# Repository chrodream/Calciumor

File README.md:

# Calciumor
## 特徴
- ESP32-S3をベースとした電卓\/無線マクロパッド
- Li-Poバッテリーによる充電に対応
- 128×64ドットのOLED表示 or 128×32ドット + 7セグ表示器

## スペック
| 項目 | Min. | Typ. | Max. | 
| :------------------------ | ---- | ---- | ---- | 
| USB入力電圧 [V] | 4.75 | 5.0 | 5.25 | 
| 消費電流 (電卓/バッテリー) [mA] | | | | 
| 消費電流(マクロパッド/バッテリー) [mA] | | | |
| 消費電流 (電卓/USB) [mA] | | | 750 |
| 消費電流(マクロパッド/USB) [mA]   | | | 750 |
| 消費電流(スリープ) [mA]    | | | | 
| バッテリー容量 [mAh] | 400 | - | - | 
| バッテリー電圧範囲 [V] | 2.9 | - | 4.2 |

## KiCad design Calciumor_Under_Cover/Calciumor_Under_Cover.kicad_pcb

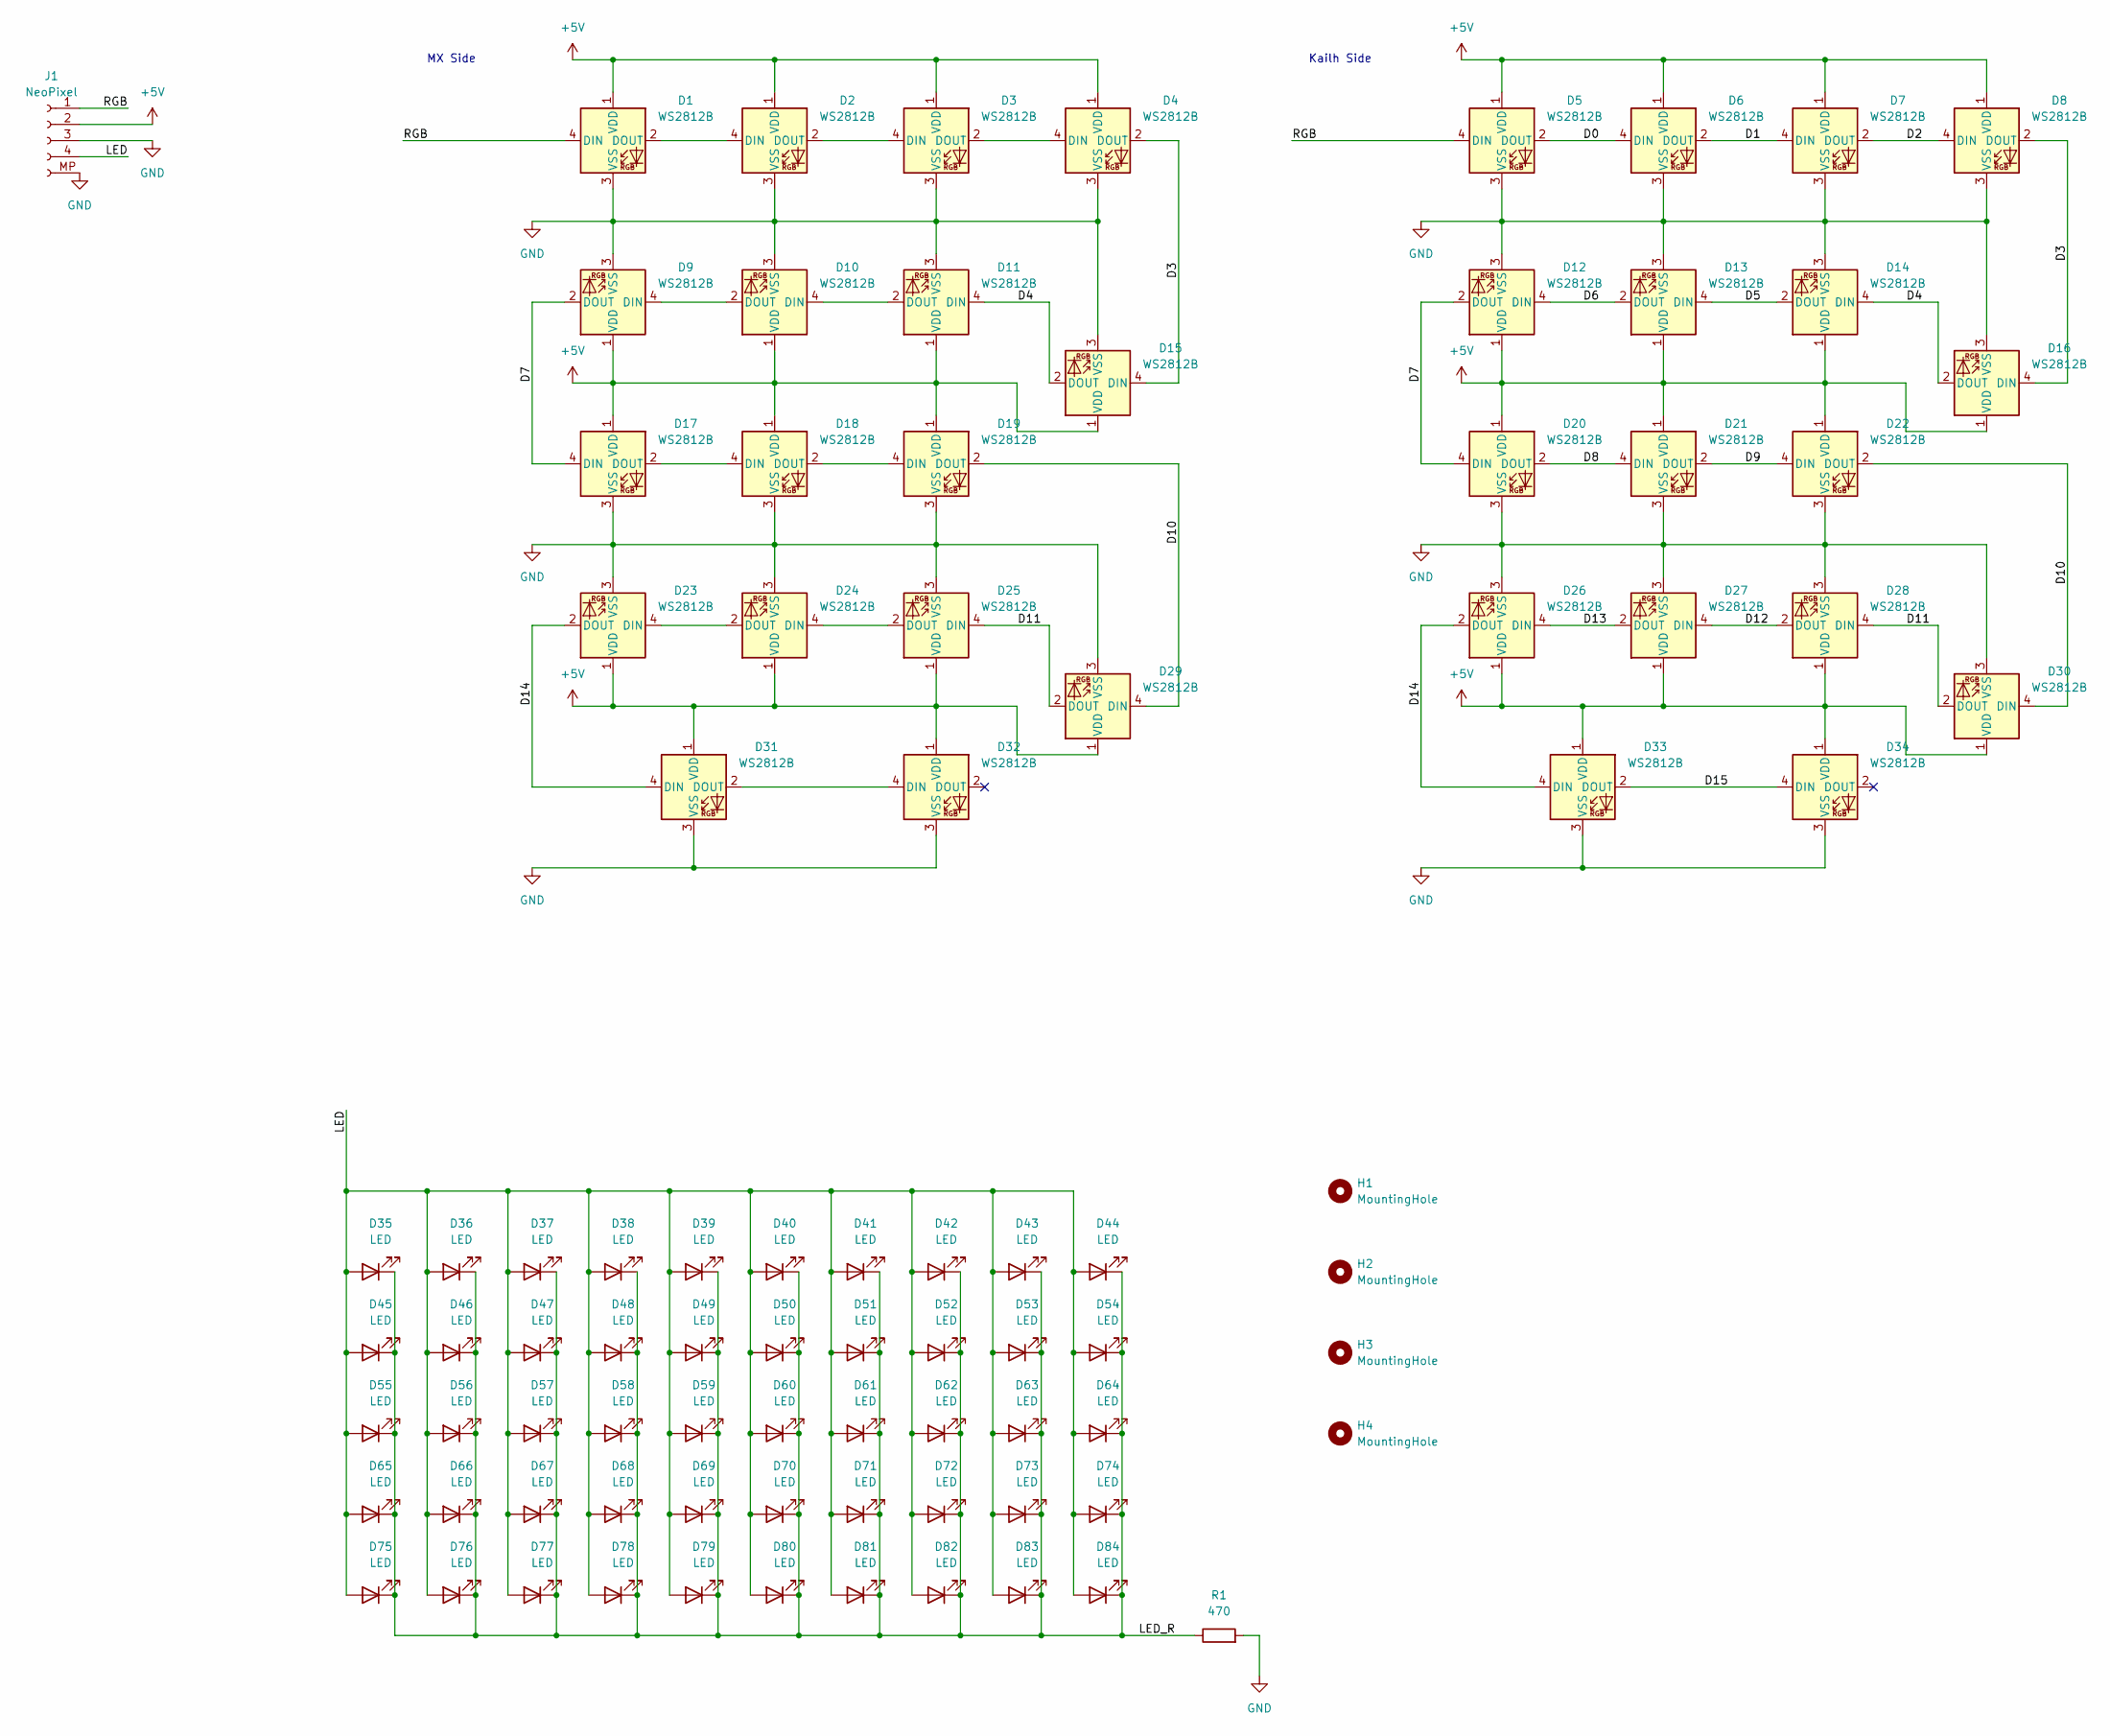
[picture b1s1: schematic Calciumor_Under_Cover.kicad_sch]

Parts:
D1, D2, D3, D4, D5, D6, D7, D8, D9, D10, D11, D12, D13, D14, D15, D16, D17, D18, D19, D20, D21, D22, D23, D24, D25, D26, D27, D28, D29, D30, D31, D32, D33, D34: WS2812B; LED_WS2812B_PLCC4_5.0x5.0mm_P3.2mm; LCSC C2843785
D35, D36, D37, D38, D39, D40, D41, D42, D43, D44, D45, D46, D47, D48, D49, D50, D51, D52, D53, D54, D55, D56, D57, D58, D59, D60, D61, D62, D63, D64, D65, D66, D67, D68, D69, D70, D71, D72, D73, D74, D75, D76, D77, D78, D79, D80, D81, D82, D83, D84: LED; LED_0603_1608Metric; LCSC C2290
H1, H2, H3, H4: MountingHole; MountingHole_2.2mm_M2
J1: NeoPixel; JST_PH_S4B-PH-SM4-TB_1x04-1MP_P2.00mm_Horizontal
R1: 470; R_1206_3216Metric

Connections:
+5V: D1.1 (VDD), D2.1 (VDD), D3.1 (VDD), D4.1 (VDD), D5.1 (VDD), D6.1 (VDD), D7.1 (VDD), D8.1 (VDD), D9.1 (VDD), D10.1 (VDD), D11.1 (VDD), D12.1 (VDD), D13.1 (VDD), D14.1 (VDD), D15.1 (VDD), D16.1 (VDD), D17.1 (VDD), D18.1 (VDD), D19.1 (VDD), D20.1 (VDD), D21.1 (VDD), D22.1 (VDD), D23.1 (VDD), D24.1 (VDD), D25.1 (VDD), D26.1 (VDD), D27.1 (VDD), D28.1 (VDD), D29.1 (VDD), D30.1 (VDD), D31.1 (VDD), D32.1 (VDD), D33.1 (VDD), D34.1 (VDD), J1.2
/D0: D5.2 (DOUT), D6.4 (DIN)
/D1: D6.2 (DOUT), D7.4 (DIN)
/D2: D7.2 (DOUT), D8.4 (DIN)
/D3: D4.2 (DOUT), D8.2 (DOUT), D15.4 (DIN), D16.4 (DIN)
/D4: D11.4 (DIN), D14.4 (DIN), D15.2 (DOUT), D16.2 (DOUT)
/D5: D13.4 (DIN), D14.2 (DOUT)
/D6: D12.4 (DIN), D13.2 (DOUT)
/D7: D9.2 (DOUT), D12.2 (DOUT), D17.4 (DIN), D20.4 (DIN)
/D8: D20.2 (DOUT), D21.4 (DIN)
/D9: D21.2 (DOUT), D22.4 (DIN)
/D10: D19.2 (DOUT), D22.2 (DOUT), D29.4 (DIN), D30.4 (DIN)
/D11: D25.4 (DIN), D28.4 (DIN), D29.2 (DOUT), D30.2 (DOUT)
/D12: D27.4 (DIN), D28.2 (DOUT)
/D13: D26.4 (DIN), D27.2 (DOUT)
/D14: D23.2 (DOUT), D26.2 (DOUT), D31.4 (DIN), D33.4 (DIN)
/D15: D33.2 (DOUT), D34.4 (DIN)
/LED: D35.2 (A), D36.2 (A), D37.2 (A), D38.2 (A), D39.2 (A), D40.2 (A), D41.2 (A), D42.2 (A), D43.2 (A), D44.2 (A), D45.2 (A), D46.2 (A), D47.2 (A), D48.2 (A), D49.2 (A), D50.2 (A), D51.2 (A), D52.2 (A), D53.2 (A), D54.2 (A), D55.2 (A), D56.2 (A), D57.2 (A), D58.2 (A), D59.2 (A), D60.2 (A), D61.2 (A), D62.2 (A), D63.2 (A), D64.2 (A), D65.2 (A), D66.2 (A), D67.2 (A), D68.2 (A), D69.2 (A), D70.2 (A), D71.2 (A), D72.2 (A), D73.2 (A), D74.2 (A), D75.2 (A), D76.2 (A), D77.2 (A), D78.2 (A), D79.2 (A), D80.2 (A), D81.2 (A), D82.2 (A), D83.2 (A), D84.2 (A), J1.4
/LED_R: D35.1 (K), D36.1 (K), D37.1 (K), D38.1 (K), D39.1 (K), D40.1 (K), D41.1 (K), D42.1 (K), D43.1 (K), D44.1 (K), D45.1 (K), D46.1 (K), D47.1 (K), D48.1 (K), D49.1 (K), D50.1 (K), D51.1 (K), D52.1 (K), D53.1 (K), D54.1 (K), D55.1 (K), D56.1 (K), D57.1 (K), D58.1 (K), D59.1 (K), D60.1 (K), D61.1 (K), D62.1 (K), D63.1 (K), D64.1 (K), D65.1 (K), D66.1 (K), D67.1 (K), D68.1 (K), D69.1 (K), D70.1 (K), D71.1 (K), D72.1 (K), D73.1 (K), D74.1 (K), D75.1 (K), D76.1 (K), D77.1 (K), D78.1 (K), D79.1 (K), D80.1 (K), D81.1 (K), D82.1 (K), D83.1 (K), D84.1 (K), R1.1
/RGB: D1.4 (DIN), D5.4 (DIN), J1.1
GND: D1.3 (VSS), D2.3 (VSS), D3.3 (VSS), D4.3 (VSS), D5.3 (VSS), D6.3 (VSS), D7.3 (VSS), D8.3 (VSS), D9.3 (VSS), D10.3 (VSS), D11.3 (VSS), D12.3 (VSS), D13.3 (VSS), D14.3 (VSS), D15.3 (VSS), D16.3 (VSS), D17.3 (VSS), D18.3 (VSS), D19.3 (VSS), D20.3 (VSS), D21.3 (VSS), D22.3 (VSS), D23.3 (VSS), D24.3 (VSS), D25.3 (VSS), D26.3 (VSS), D27.3 (VSS), D28.3 (VSS), D29.3 (VSS), D30.3 (VSS), D31.3 (VSS), D32.3 (VSS), D33.3 (VSS), D34.3 (VSS), J1.3, J1.MP (Pin_5), R1.2
unnamed: D1.2 (DOUT), D2.4 (DIN)
unnamed: D2.2 (DOUT), D3.4 (DIN)
unnamed: D3.2 (DOUT), D4.4 (DIN)
unnamed: D10.4 (DIN), D11.2 (DOUT)
unnamed: D9.4 (DIN), D10.2 (DOUT)
unnamed: D17.2 (DOUT), D18.4 (DIN)
unnamed: D18.2 (DOUT), D19.4 (DIN)
unnamed: D23.4 (DIN), D24.2 (DOUT)
unnamed: D24.4 (DIN), D25.2 (DOUT)
unnamed: D31.2 (DOUT), D32.4 (DIN)

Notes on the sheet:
Kailh Side
MX Side

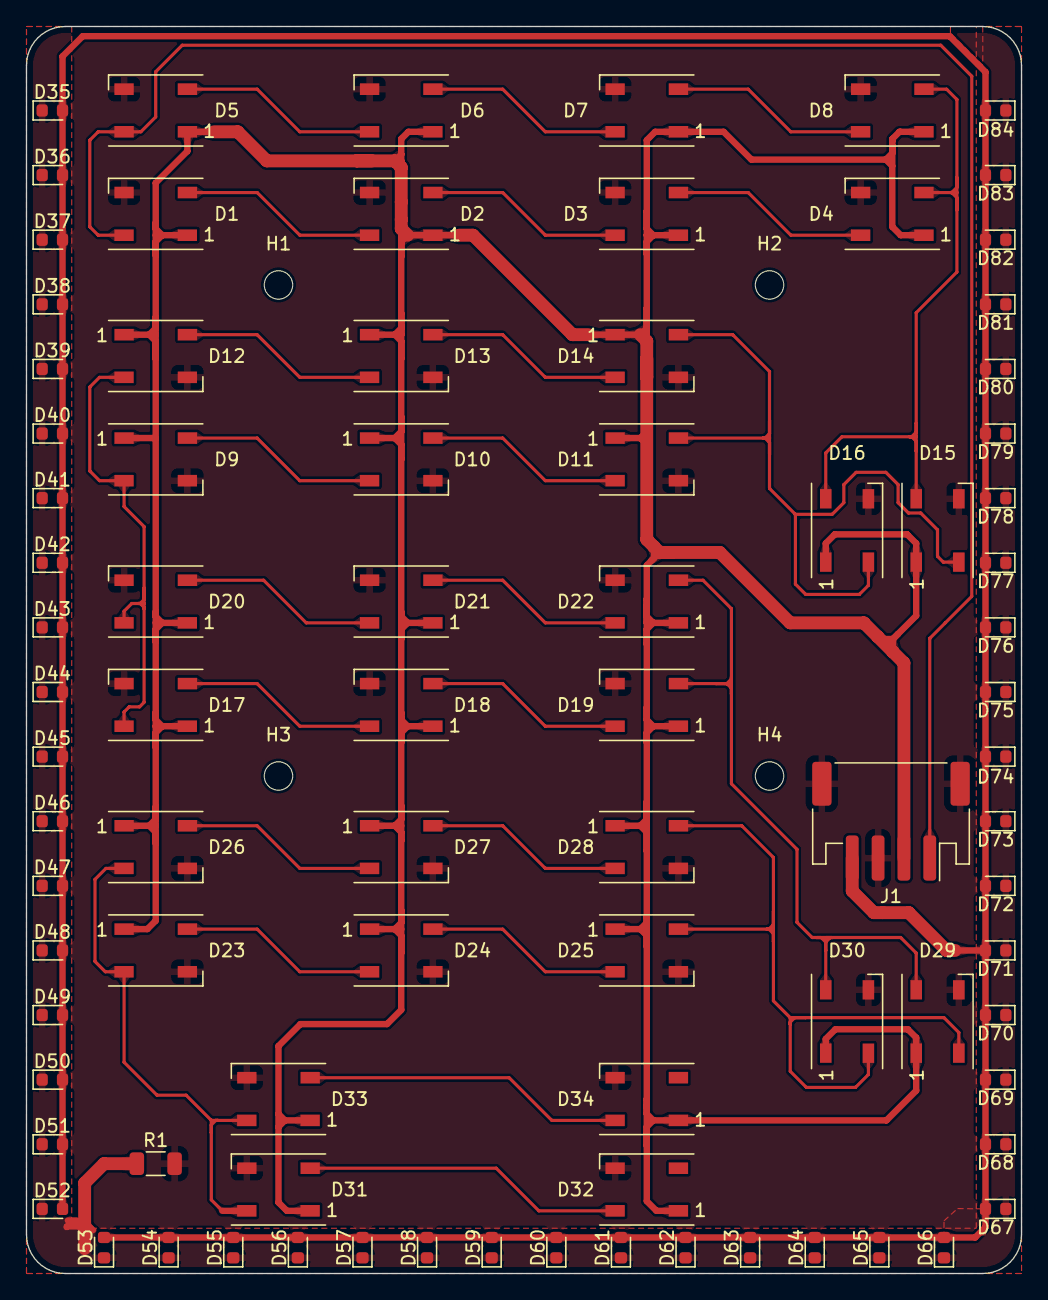
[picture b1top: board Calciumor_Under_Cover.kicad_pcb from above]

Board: 2 copper layers, 77.0 x 96.5 mm, 90 parts (0 on the bottom side), 31 nets.

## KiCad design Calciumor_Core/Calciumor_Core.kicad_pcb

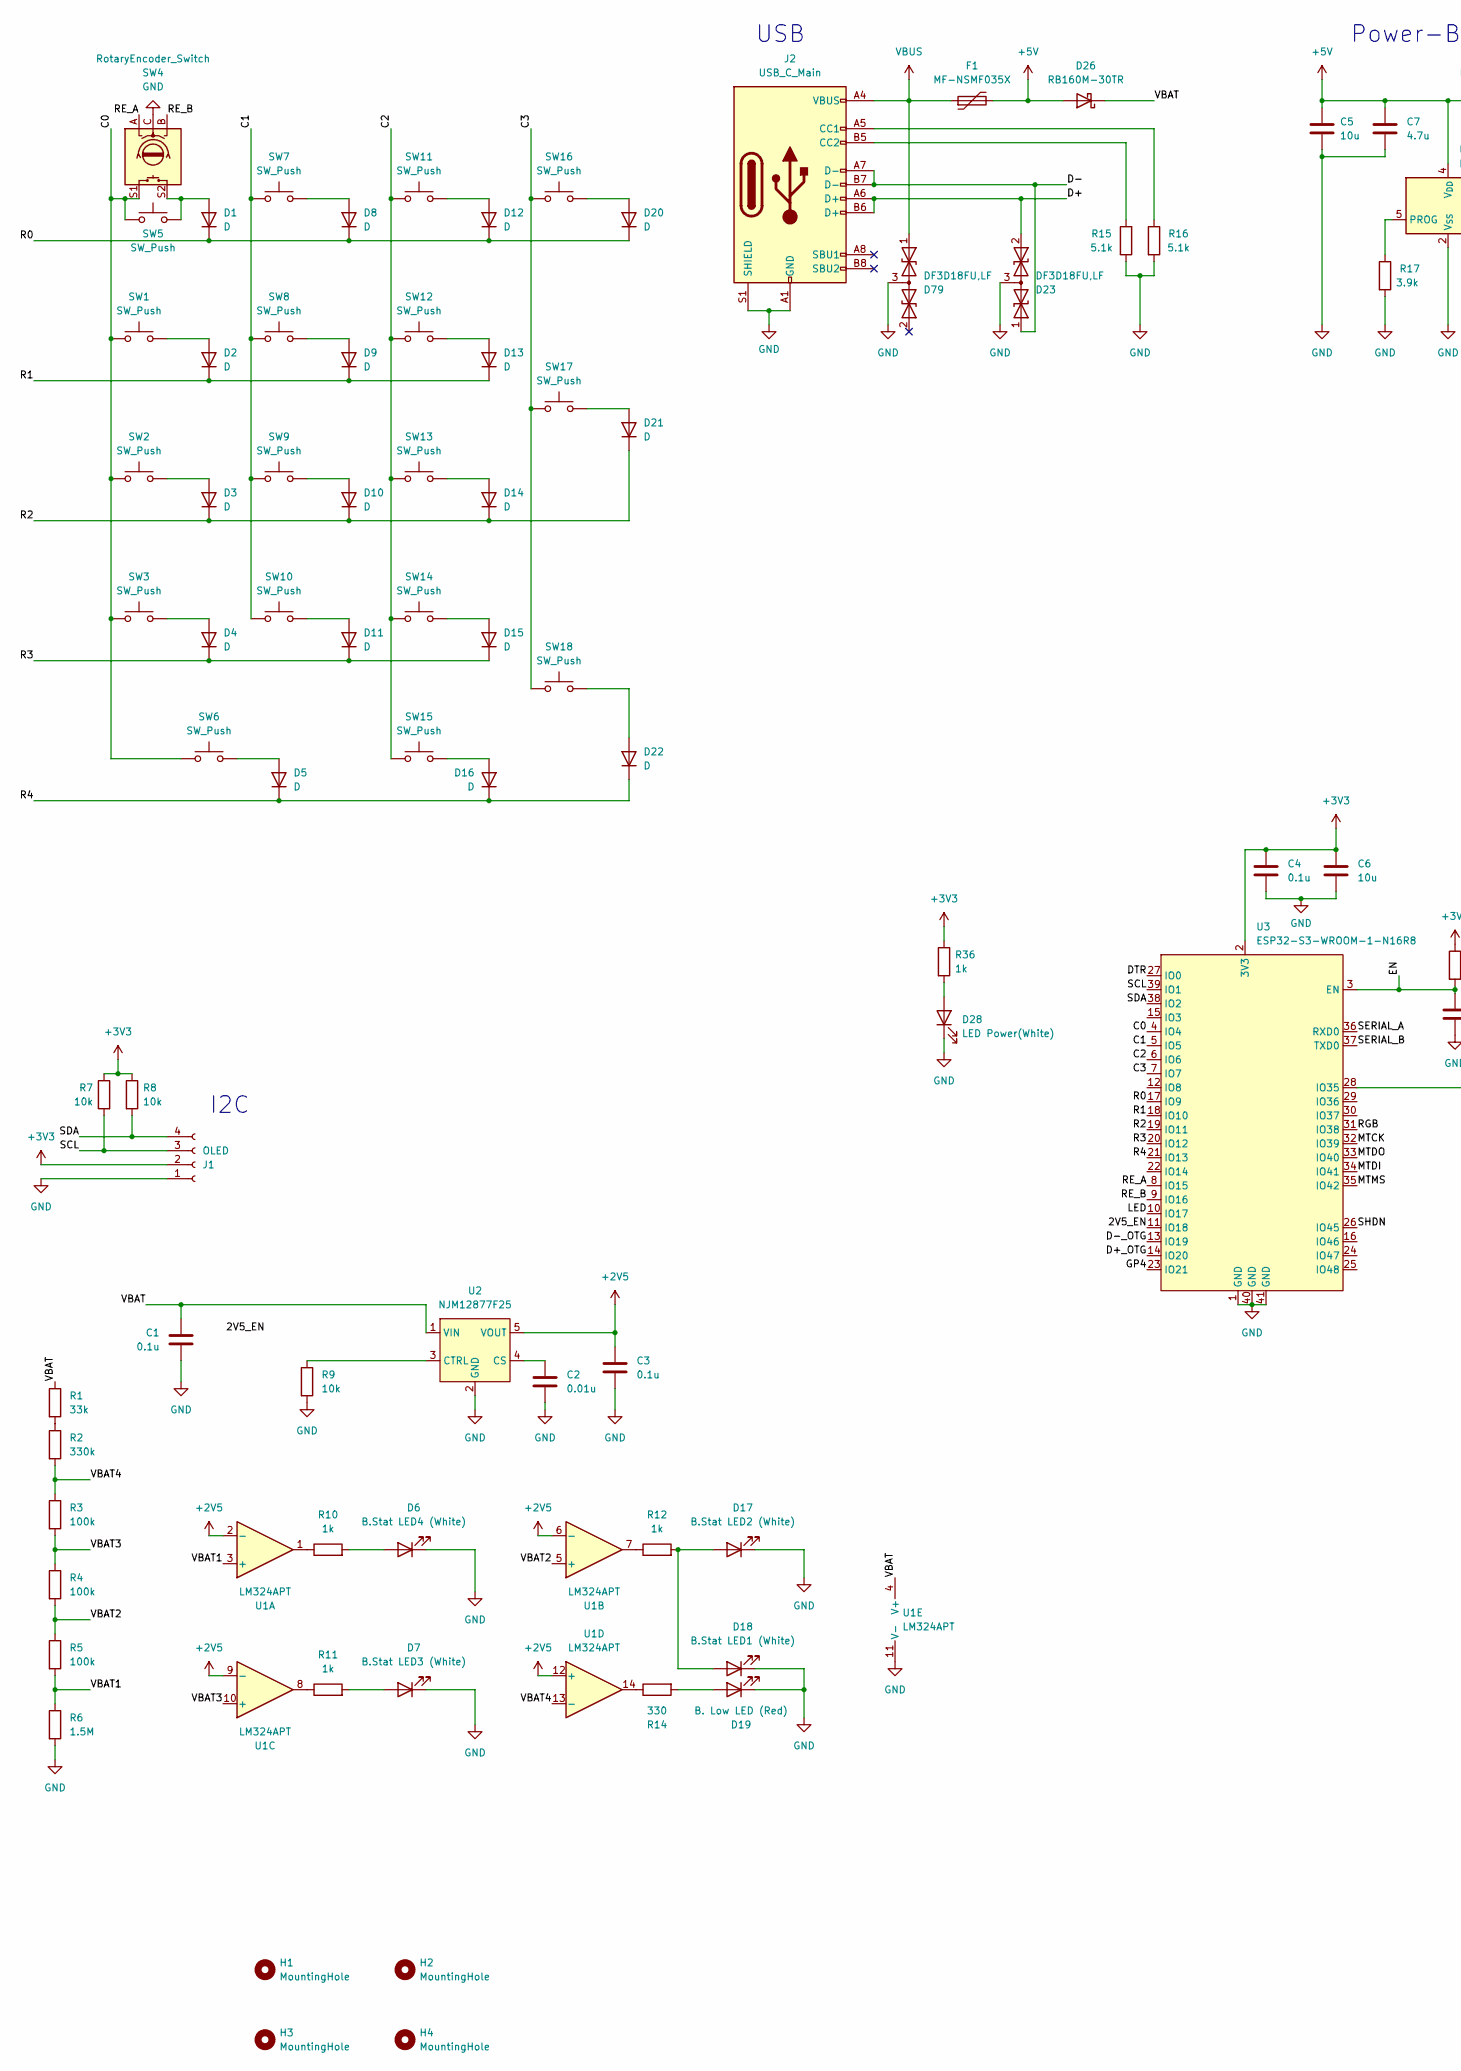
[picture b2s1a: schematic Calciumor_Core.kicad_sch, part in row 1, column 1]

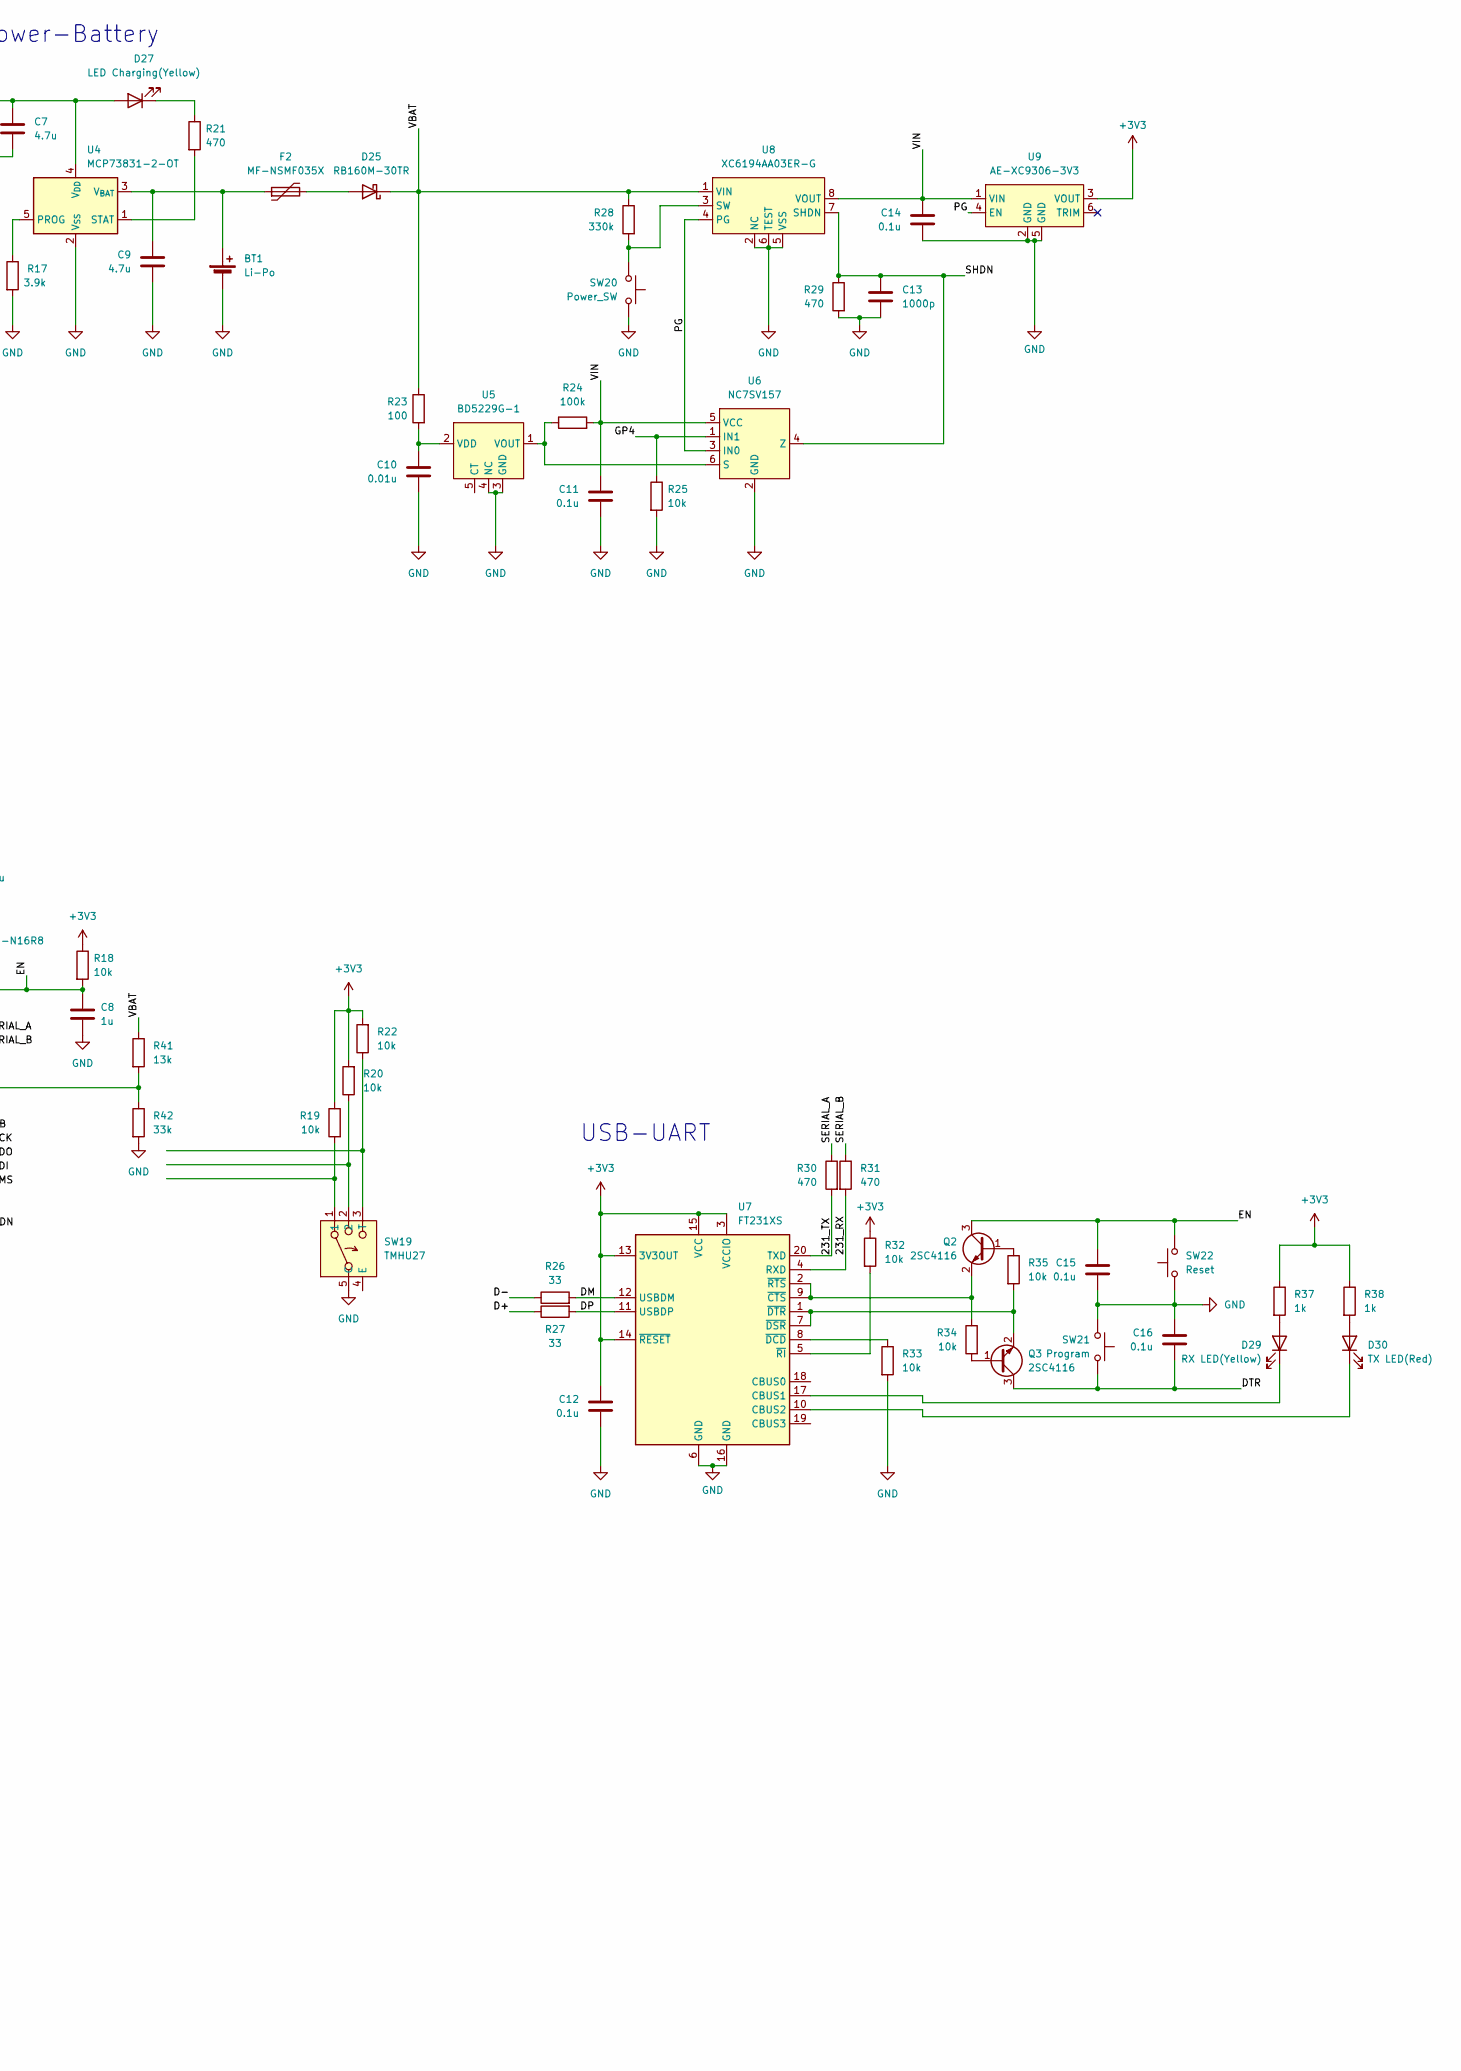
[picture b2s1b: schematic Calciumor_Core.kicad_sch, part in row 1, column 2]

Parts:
BT1: Li-Po; JST_PH_S2B-PH-K_1x02_P2.00mm_Horizontal
C1, C3, C4, C11, C12, C14, C15, C16: 0.1u; C_0402_1005Metric; LCSC C307331
C2, C10: 0.01u; C_0402_1005Metric; LCSC C15195
C5, C6: 10u; C_0805_2012Metric; LCSC C15850
C7, C9: 4.7u; C_0603_1608Metric; LCSC C19666
C8: 1u; C_0402_1005Metric; LCSC C52923
C13: 1000p; C_0402_1005Metric; LCSC C307331
D1, D2, D3, D4, D5, D8, D9, D10, D11, D12, D13, D14, D15, D16, D20, D21, D22: D; SOD-123; LCSC C81598
D6: B.Stat LED4 (White); LED_0603_1608Metric; LCSC C2290
D7: B.Stat LED3 (White); LED_0603_1608Metric; LCSC C2290
D17: B.Stat LED2 (White); LED_0603_1608Metric; LCSC C2290
D18: B.Stat LED1 (White); LED_0603_1608Metric; LCSC C2290
D19: B. Low LED (Red); LED_0603_1608Metric; LCSC C2286
D23, D79: DF3D18FU,LF; SOT-323_SC-70
D25, D26: RB160M-30TR; D_SOD-123F
D27: LED Charging(Yellow); LED_0603_1608Metric; LCSC C72038
D28: LED Power(White); LED_0603_1608Metric; LCSC C2290
D29: RX LED(Yellow); LED_0603_1608Metric; LCSC C72038
D30: TX LED(Red); LED_0603_1608Metric; LCSC C2286
F1, F2: MF-NSMF035X; MF-NSMF
H1, H2, H3, H4: MountingHole; MountingHole_2.2mm_M2
J1: OLED; PinHeader_1x04_P2.54mm_Horizontal
J2: USB_C_Main; USB_C_Receptacle_G-Switch_GT-USB-7010ASV; LCSC C2988369
Q2, Q3: 2SC4116; SOT-323_SC-70
R1: 33k; R_0603_1608Metric; LCSC C22967
R2: 330k; R_0603_1608Metric; LCSC C22807
R3, R4, R5: 100k; R_0402_1005Metric; LCSC C25779
R6: 1.5M; R_0603_1608Metric; LCSC C23178
R7, R8, R9, R18, R19, R20, R22, R25, R32, R33, R34, R35: 10k; R_0402_1005Metric; LCSC C25744
R10, R11, R12, R36, R37, R38: 1k; R_0402_1005Metric; LCSC C11702
R14: 330; R_0402_1005Metric; LCSC C11702
R15, R16: 5.1k; R_0402_1005Metric; LCSC C25905
R17: 3.9k; R_1206_3216Metric
R21, R29, R30, R31: 470; R_0402_1005Metric; LCSC C25117
R23: 100; R_0603_1608Metric; LCSC C22775
R24: 100k; R_0402_1005Metric; LCSC C25741
R26, R27: 33; R_0603_1608Metric; LCSC C23140
R28: 330k; R_0402_1005Metric; LCSC C23137
R41: 13k; R_0603_1608Metric; LCSC C22797
R42: 33k; R_0402_1005Metric; LCSC C22967
SW1, SW2, SW3, SW5, SW6, SW7, SW8, SW9, SW10, SW11, SW12, SW13, SW14, SW15, SW16, SW17, SW18: SW_Push; MX_Choc_Socket
SW4: RotaryEncoder_Switch; EC12
SW19: TMHU27
SW20: Power_SW; THBP07
SW21: Program; TVAF06
SW22: Reset; TVAF06
U1: LM324APT; TSSOP-14_4.4x5mm_P0.65mm; LCSC C111180
U2: NJM12877F25; SOT-23-5
U3: ESP32-S3-WROOM-1-N16R8; ESP32-S3-WROOM-1
U4: MCP73831-2-OT; SOT-23-5
U5: BD5229G-1; SOT-23-5
U6: NC7SV157; SOT-363_SC-70-6
U7: FT231XS; SSOP-20_3.9x8.7mm_P0.635mm; LCSC C89607
U8: XC6194AA03ER-G; XC6194; LCSC C18221112
U9: AE-XC9306-3V3

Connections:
+2V5: C3.1, U1.2 (-), U1.6 (-), U1.9 (-), U1.12 (+), U2.5 (VOUT)
+3V3: C4.1, C6.1, C12.1, J1.2, R7.1, R8.1, R18.1, R19.1, R20.2, R22.2, R32.1, R36.1, R37.1, R38.1, U3.2 (3V3), U7.3 (VCCIO), U7.13 (3V3OUT), U7.14 (~RESET), U7.15 (VCC), U9.3 (VOUT)
+5V: C5.1, C7.1, D26.2 (A), D27.2 (A), F1.2, U4.4 (V_{DD})
/2V5_EN: U3.11 (IO18)
/231_RX: R31.2, U7.4 (RXD)
/231_TX: R30.2, U7.20 (TXD)
/C0: SW1.1, SW2.1, SW3.1, SW4.S1, SW5.1, SW6.1, U3.4 (IO4)
/C1: SW7.1, SW8.1, SW9.1, SW10.1, U3.5 (IO5)
/C2: SW11.1, SW12.1, SW13.1, SW14.1, SW15.1, U3.6 (IO6)
/C3: SW16.1, SW17.2, SW18.2, U3.7 (IO7)
/D+: D23.2 (A2), J2.A6 (D+), J2.B6 (D+), R27.1
/D+_OTG: U3.14 (IO20)
/D-: D23.1 (A1), J2.A7 (D-), J2.B7 (D-), R26.1
/D-_OTG: U3.13 (IO19)
/DM: R26.2, U7.12 (USBDM)
/DP: R27.2, U7.11 (USBDP)
/DTR: C16.2, Q3.3 (C), SW21.1, U3.27 (IO0)
/EN: C8.1, C15.1, Q2.3 (C), R18.2, SW22.2, U3.3 (EN)
/GP4: R25.1, U3.23 (IO21), U6.1 (IN1)
/LED: U3.10 (IO17)
/MTCK: U3.32 (IO39)
/MTDI: U3.34 (IO41)
/MTDO: U3.33 (IO40)
/MTMS: U3.35 (IO42)
/PG: U6.3 (IN0), U8.4 (PG), U9.4 (EN)
/R0: D1.1 (K), D8.1 (K), D12.1 (K), D20.1 (K), U3.17 (IO9)
/R1: D2.1 (K), D9.1 (K), D13.1 (K), U3.18 (IO10)
/R2: D3.1 (K), D10.1 (K), D14.1 (K), D21.1 (K), U3.19 (IO11)
/R3: D4.1 (K), D11.1 (K), D15.1 (K), U3.20 (IO12)
/R4: D5.1 (K), D16.1 (K), D22.1 (K), U3.21 (IO13)
/RE_A: SW4.A, U3.8 (IO15)
/RE_B: SW4.B, U3.9 (IO16)
/RGB: U3.31 (IO38)
/SCL: J1.3, R7.2, U3.39 (IO1)
/SDA: J1.4, R8.2, U3.38 (IO2)
/SERIAL_A: R30.1, U3.36 (RXD0)
/SERIAL_B: R31.1, U3.37 (TXD0)
/SHDN: C13.1, R29.1, U3.26 (IO45), U6.4 (Z), U8.7 (SHDN)
/VBAT: C1.1, D25.1 (K), D26.1 (K), R1.1, R23.1, R28.1, R41.1, U1.4 (V+), U2.1 (VIN), U8.1 (VIN)
/VBAT1: R5.2, R6.1, U1.3 (+)
/VBAT2: R4.2, R5.1, U1.5 (+)
/VBAT3: R3.2, R4.1, U1.10 (+)
/VBAT4: R2.2, R3.1, U1.13 (-)
/VIN: C11.1, C14.1, R24.2, U6.5 (VCC), U8.8 (VOUT), U9.1 (VIN)
GND: BT1.2 (-), C1.2, C2.2, C3.2, C4.2, C5.2, C6.2, C7.2, C8.2, C9.2, C10.2, C11.2, C12.2, C13.2, C14.2, C15.2, C16.1, D6.1 (K), D7.1 (K), D17.1 (K), D18.1 (K), D19.1 (K), D23.3 (common), D28.1 (K), D79.3 (common), J1.1, J2.A1 (GND), J2.A12 (GND), J2.B1 (GND), J2.B12 (GND), J2.S1 (SHIELD), R6.2, R9.2, R15.1, R16.2, R17.2, R25.2, R29.2, R33.2, R42.2, SW4.C, SW19.5 (C), SW20.1, SW21.2, SW22.1, U1.11 (V-), U2.2 (GND), U3.1 (GND), U3.40 (GND), U3.41 (GND), U4.2 (V_{SS}), U5.3 (GND), U5.4 (NC), U6.2 (GND), U7.6 (GND), U7.16 (GND), U8.2 (NC), U8.5 (VSS), U8.6 (TEST), U9.2 (GND), U9.5 (GND)
unnamed: BT1.1 (+), C9.1, F2.1, U4.3 (V_{BAT})
unnamed: D1.2 (A), SW4.S2, SW5.2
unnamed: D2.2 (A), SW1.2
unnamed: D3.2 (A), SW2.2
unnamed: D4.2 (A), SW3.2
unnamed: D5.2 (A), SW6.2
unnamed: D6.2 (A), R10.2
unnamed: D7.2 (A), R11.2
unnamed: D8.2 (A), SW7.2
unnamed: D9.2 (A), SW8.2
unnamed: D10.2 (A), SW9.2
unnamed: D11.2 (A), SW10.2
unnamed: D12.2 (A), SW11.2
unnamed: D13.2 (A), SW12.2
unnamed: D14.2 (A), SW13.2
unnamed: D15.2 (A), SW14.2
unnamed: D16.2 (A), SW15.2
unnamed: D17.2 (A), D18.2 (A), R12.2
unnamed: D19.2 (A), R14.2
unnamed: D20.2 (A), SW16.2
unnamed: D21.2 (A), SW17.1
unnamed: D22.2 (A), SW18.1
unnamed: D25.2 (A), F2.2
unnamed: D27.1 (K), R21.1
unnamed: D28.2 (A), R36.2
unnamed: D29.2 (A), R37.2
unnamed: D29.1 (K), U7.17 (CBUS1)
unnamed: D30.2 (A), R38.2
unnamed: D30.1 (K), U7.10 (CBUS2)
unnamed: J2.A5 (CC1), R16.1
unnamed: J2.B5 (CC2), R15.2
unnamed: Q2.1 (B), R35.1
unnamed: Q2.2 (E), R34.1, U7.2 (~RTS), U7.9 (~CTS)
unnamed: Q3.1 (B), R34.2
unnamed: Q3.2 (E), R35.2, U7.1 (~DTR), U7.7 (~DSR)
unnamed: R1.2, R2.1
unnamed: R10.1, U1.1
unnamed: R11.1, U1.8
unnamed: R12.1, U1.7
unnamed: R14.1, U1.14
unnamed: R19.2, SW19.1
unnamed: R20.1, SW19.2
unnamed: R22.1, SW19.3 (T)
unnamed: C2.1, U2.4 (CS)
unnamed: R9.1, U2.3 (CTRL)
unnamed: R41.2, R42.1, U3.28 (IO35)
unnamed: R17.1, U4.5 (PROG)
unnamed: R21.2, U4.1 (STAT)
unnamed: C10.1, R23.2, U5.2 (VDD)
unnamed: R24.1, U5.1 (VOUT), U6.6 (S)
unnamed: R33.1, U7.8 (~DCD)
unnamed: R32.2, U7.5 (~RI)
unnamed: R28.2, SW20.2, U8.3 (SW)
VBUS: D79.1 (A1), F1.1, J2.A4 (VBUS), J2.A9 (VBUS), J2.B4 (VBUS), J2.B9 (VBUS)

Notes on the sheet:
USB
I2C
Power-Battery
USB-UART

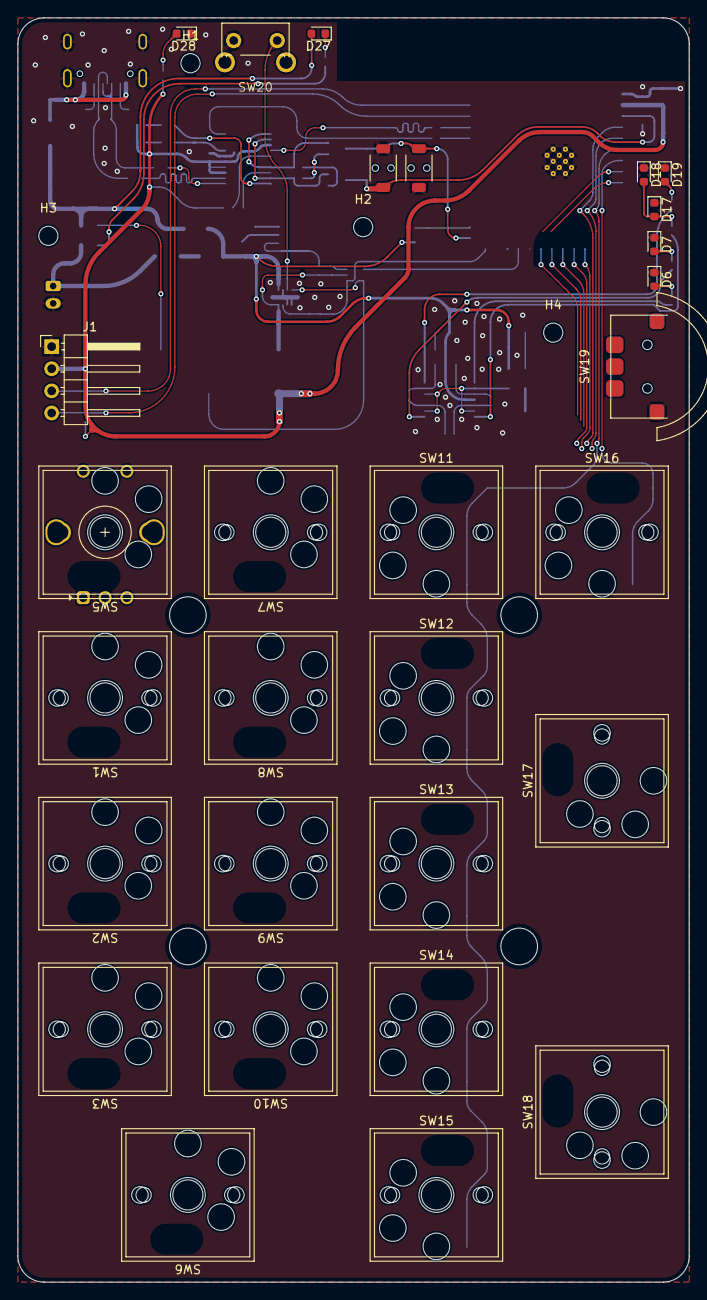
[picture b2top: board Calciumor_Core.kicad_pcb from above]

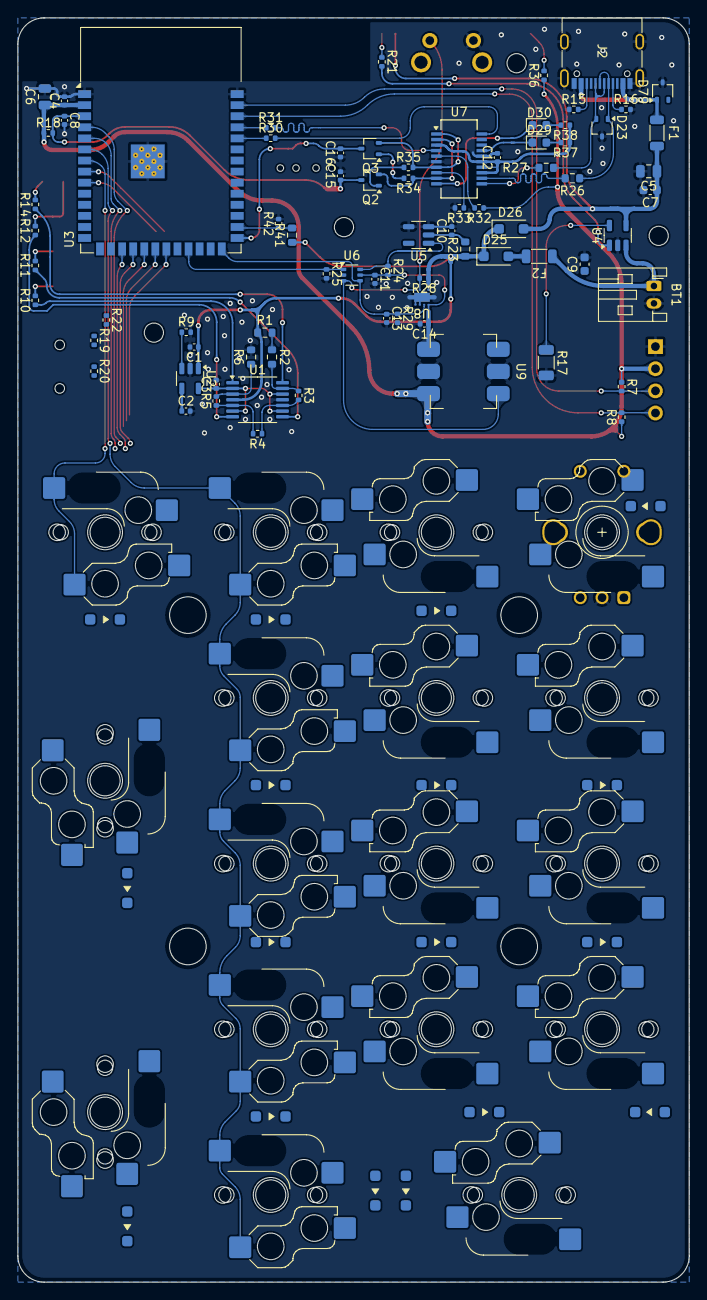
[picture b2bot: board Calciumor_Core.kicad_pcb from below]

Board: 2 copper layers, 77.0 x 145.0 mm, 127 parts (93 on the bottom side), 90 nets.

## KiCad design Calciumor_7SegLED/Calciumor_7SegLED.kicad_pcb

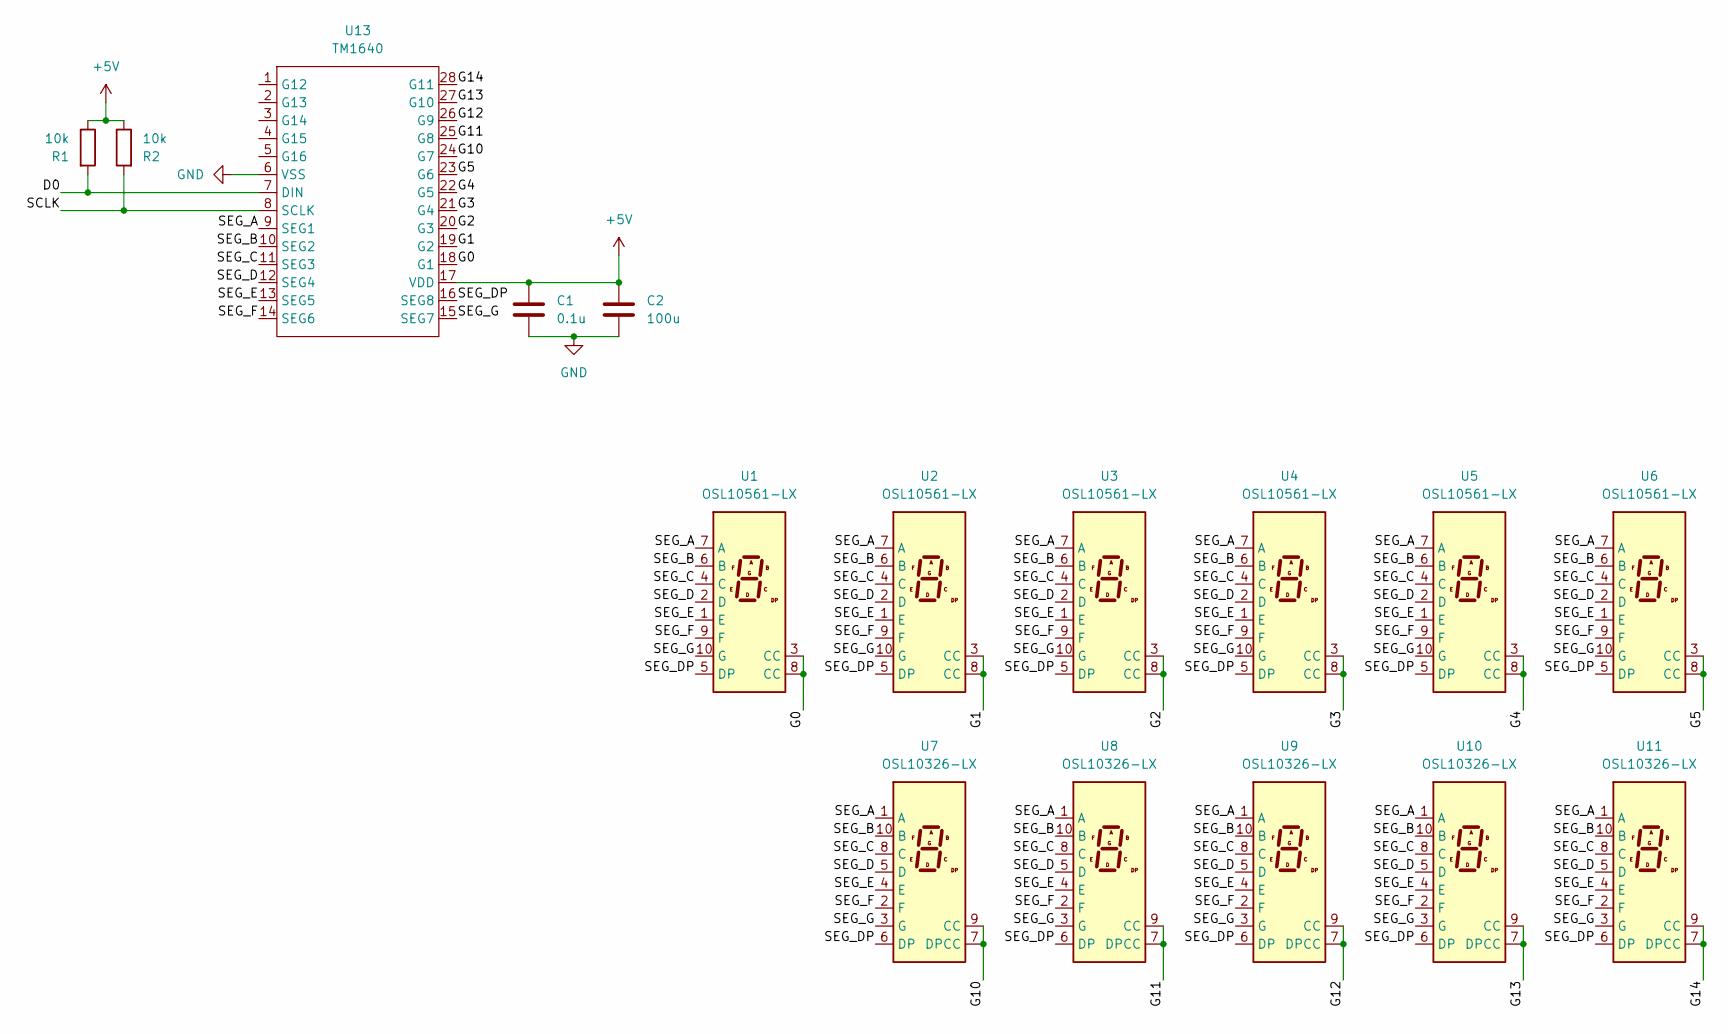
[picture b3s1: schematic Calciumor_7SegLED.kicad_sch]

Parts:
C1: 0.1u; C_0603_1608Metric_Pad1.08x0.95mm_HandSolder
C2: 100u; C_0603_1608Metric_Pad1.08x0.95mm_HandSolder
R1, R2: 10k; R_0603_1608Metric_Pad0.98x0.95mm_HandSolder
U1, U2, U3, U4, U5, U6: OSL10561-LX
U7, U8, U9, U10, U11: OSL10326-LX
U13: TM1640

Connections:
+5V: C1.1, C2.1, R1.1, R2.1, U13.17 (VDD); also elsewhere on the board
/D0: R1.2, U13.7 (DIN)
/G0: U1.3 (CC), U1.8 (CC), U13.18 (G1)
/G1: U2.3 (CC), U2.8 (CC), U13.19 (G2)
/G2: U3.3 (CC), U3.8 (CC), U13.20 (G3)
/G3: U4.3 (CC), U4.8 (CC), U13.21 (G4)
/G4: U5.3 (CC), U5.8 (CC), U13.22 (G5)
/G5: U6.3 (CC), U6.8 (CC), U13.23 (G6)
/G10: U7.7 (DPCC), U7.9 (CC), U13.24 (G7)
/G11: U8.7 (DPCC), U8.9 (CC), U13.25 (G8)
/G12: U9.7 (DPCC), U9.9 (CC), U13.26 (G9)
/G13: U10.7 (DPCC), U10.9 (CC), U13.27 (G10)
/G14: U11.7 (DPCC), U11.9 (CC), U13.28 (G11)
/SCLK: R2.2, U13.8 (SCLK)
/SEG_A: U1.7 (A), U2.7 (A), U3.7 (A), U4.7 (A), U5.7 (A), U6.7 (A), U7.1 (A), U8.1 (A), U9.1 (A), U10.1 (A), U11.1 (A), U13.9 (SEG1)
/SEG_B: U1.6 (B), U2.6 (B), U3.6 (B), U4.6 (B), U5.6 (B), U6.6 (B), U7.10 (B), U8.10 (B), U9.10 (B), U10.10 (B), U11.10 (B), U13.10 (SEG2)
/SEG_C: U1.4 (C), U2.4 (C), U3.4 (C), U4.4 (C), U5.4 (C), U6.4 (C), U7.8 (C), U8.8 (C), U9.8 (C), U10.8 (C), U11.8 (C), U13.11 (SEG3)
/SEG_D: U1.2 (D), U2.2 (D), U3.2 (D), U4.2 (D), U5.2 (D), U6.2 (D), U7.5 (D), U8.5 (D), U9.5 (D), U10.5 (D), U11.5 (D), U13.12 (SEG4)
/SEG_DP: U1.5 (DP), U2.5 (DP), U3.5 (DP), U4.5 (DP), U5.5 (DP), U6.5 (DP), U7.6 (DP), U8.6 (DP), U9.6 (DP), U10.6 (DP), U11.6 (DP), U13.16 (SEG8)
/SEG_E: U1.1 (E), U2.1 (E), U3.1 (E), U4.1 (E), U5.1 (E), U6.1 (E), U7.4 (E), U8.4 (E), U9.4 (E), U10.4 (E), U11.4 (E), U13.13 (SEG5)
/SEG_F: U1.9 (F), U2.9 (F), U3.9 (F), U4.9 (F), U5.9 (F), U6.9 (F), U7.2 (F), U8.2 (F), U9.2 (F), U10.2 (F), U11.2 (F), U13.14 (SEG6)
/SEG_G: U1.10 (G), U2.10 (G), U3.10 (G), U4.10 (G), U5.10 (G), U6.10 (G), U7.3 (G), U8.3 (G), U9.3 (G), U10.3 (G), U11.3 (G), U13.15 (SEG7)
GND: C1.2, C2.2, U13.6 (VSS); also elsewhere on the board
